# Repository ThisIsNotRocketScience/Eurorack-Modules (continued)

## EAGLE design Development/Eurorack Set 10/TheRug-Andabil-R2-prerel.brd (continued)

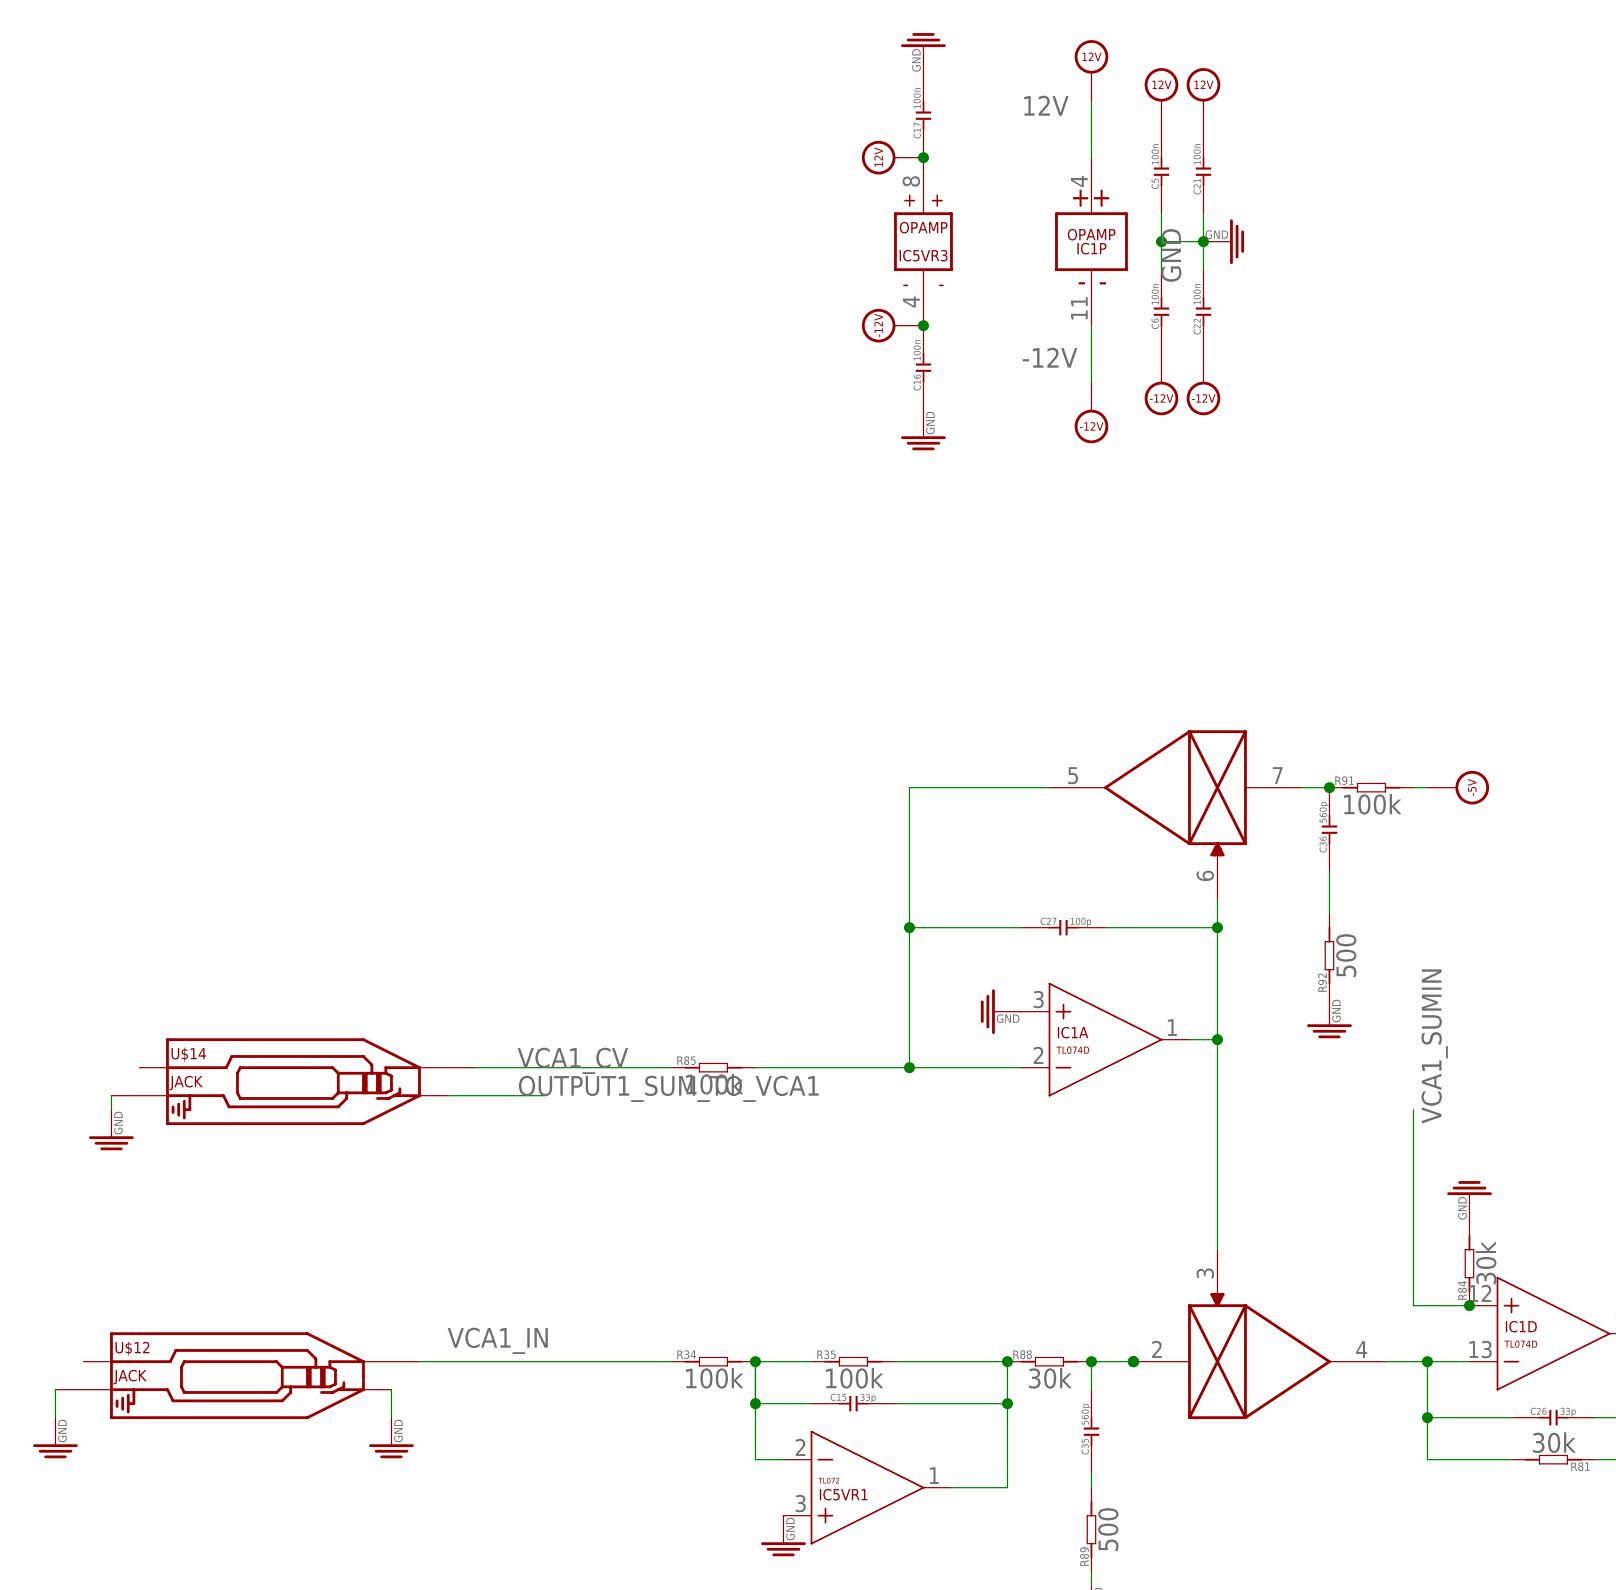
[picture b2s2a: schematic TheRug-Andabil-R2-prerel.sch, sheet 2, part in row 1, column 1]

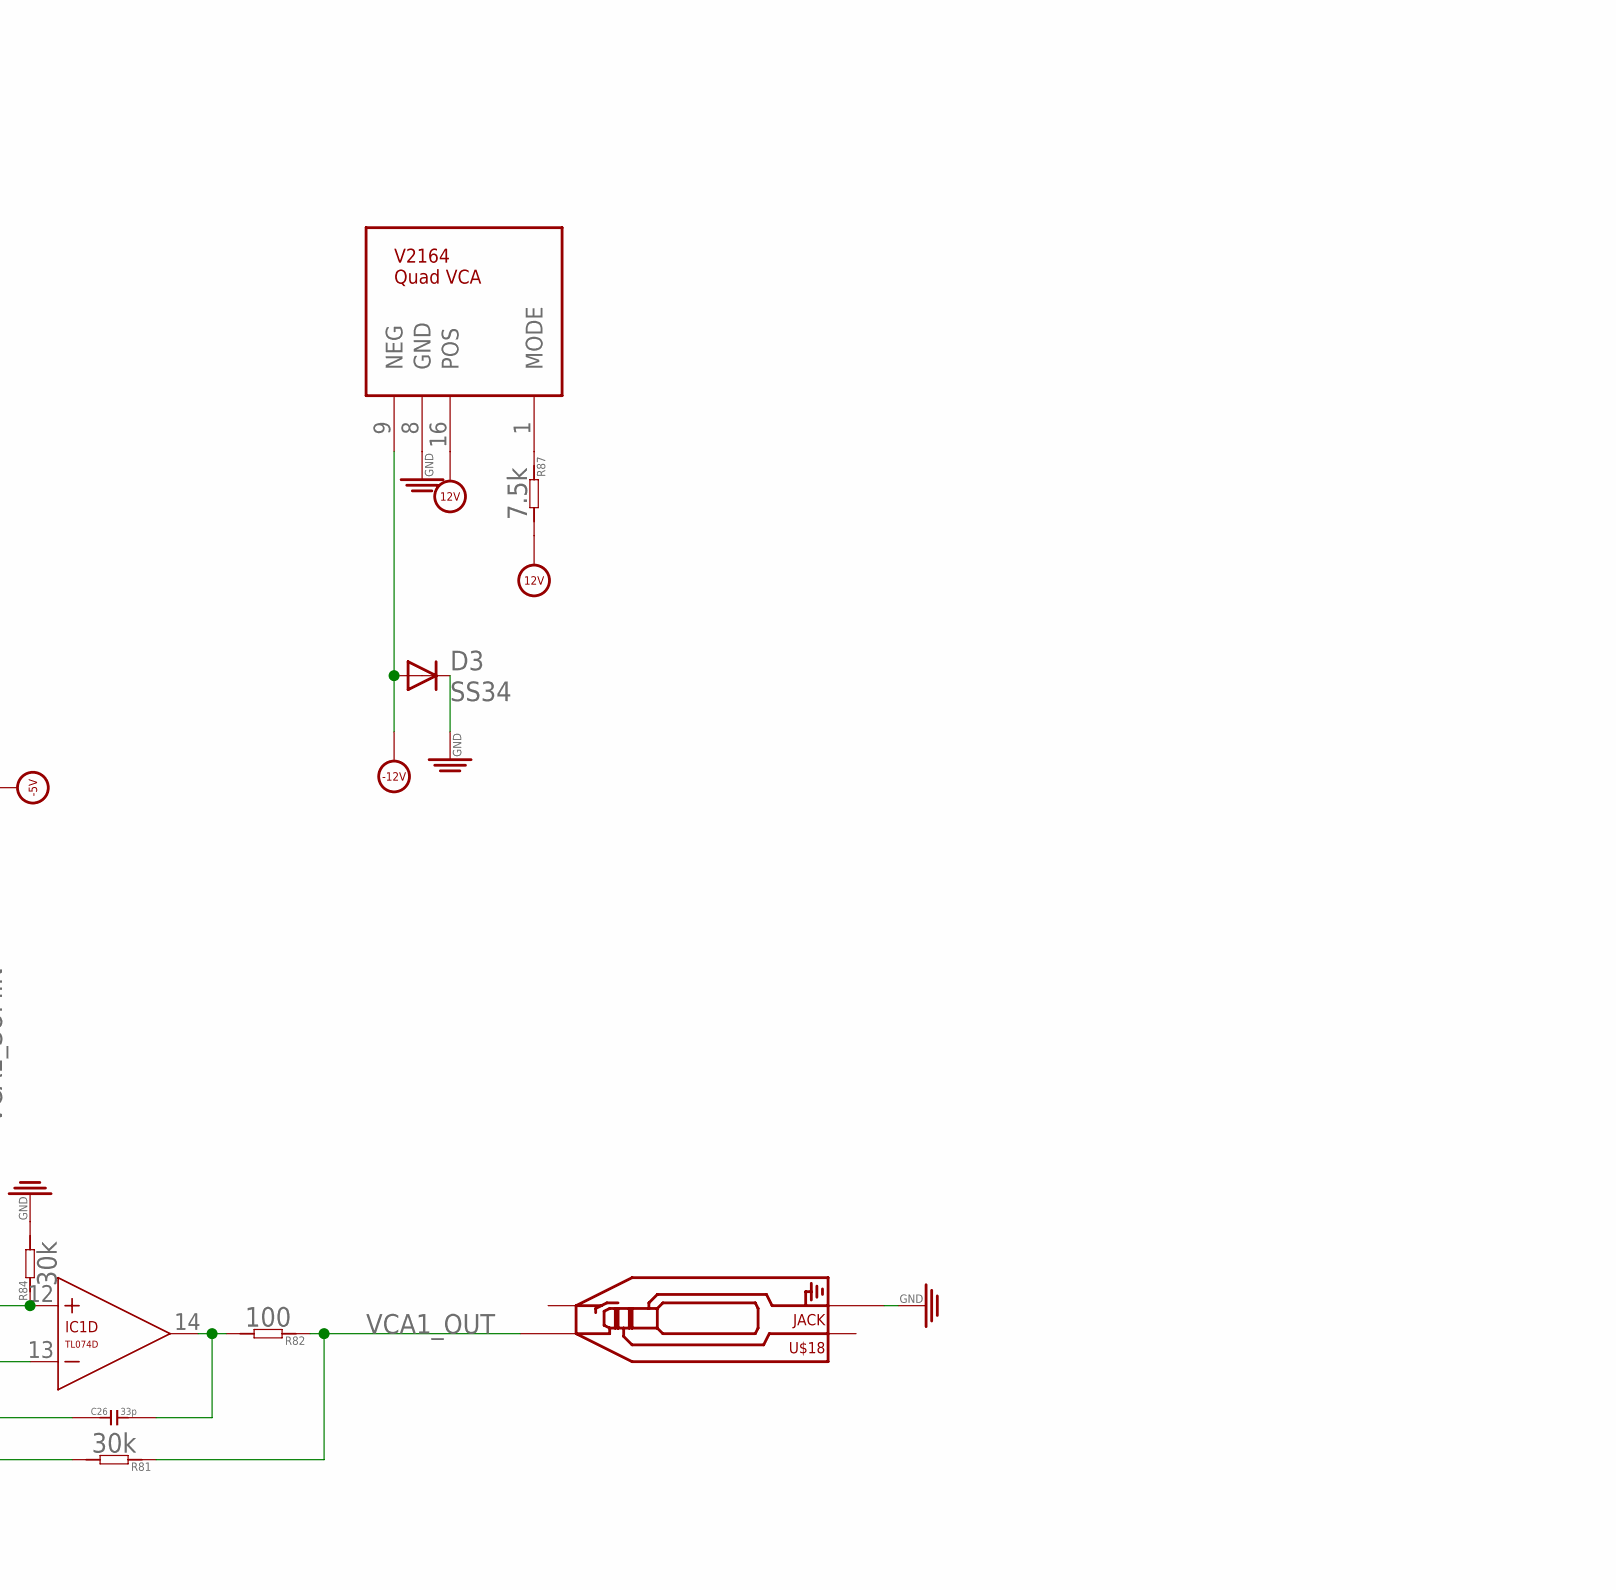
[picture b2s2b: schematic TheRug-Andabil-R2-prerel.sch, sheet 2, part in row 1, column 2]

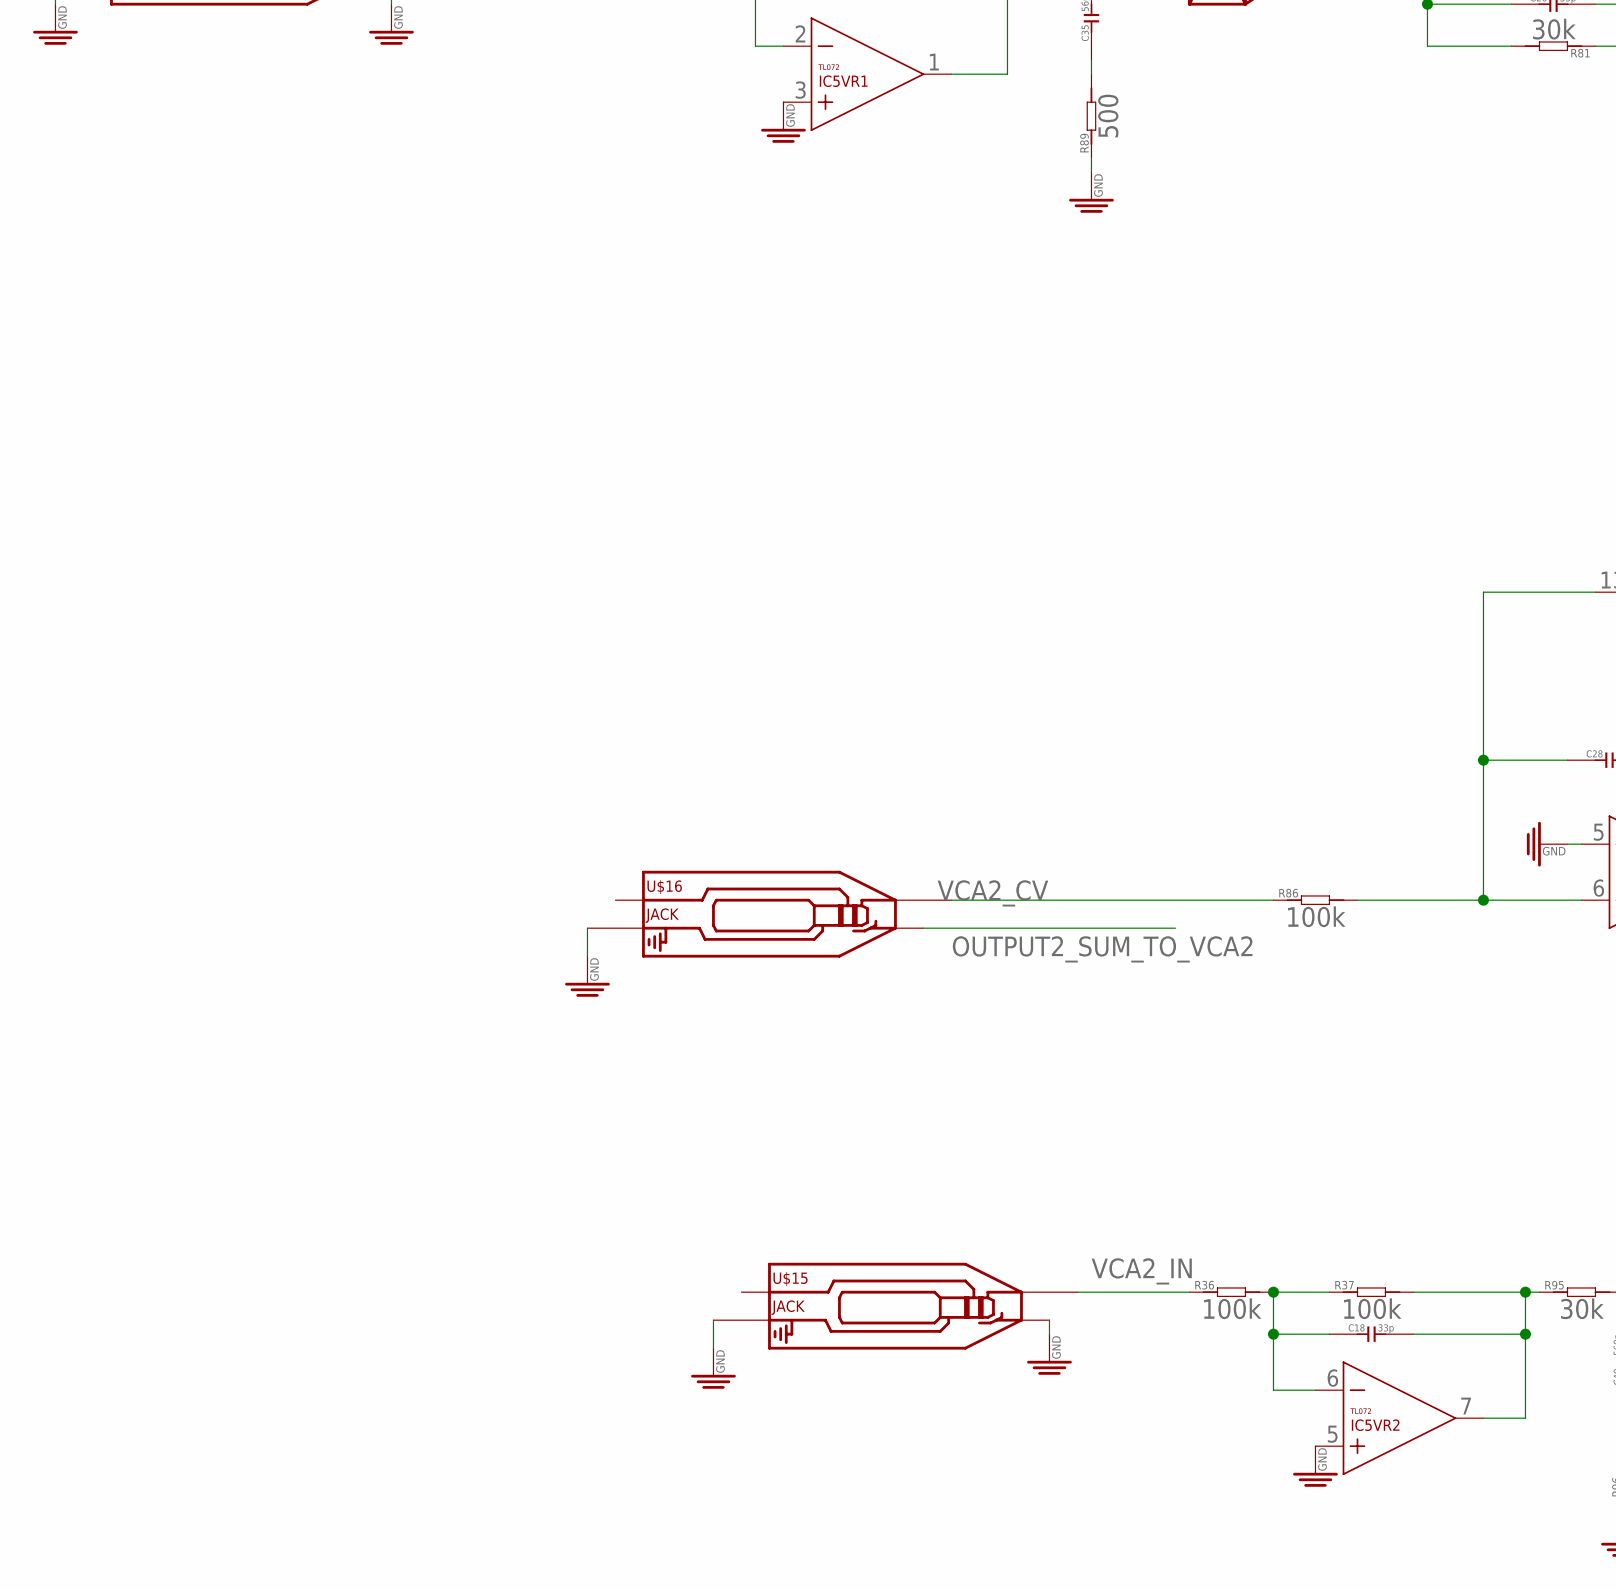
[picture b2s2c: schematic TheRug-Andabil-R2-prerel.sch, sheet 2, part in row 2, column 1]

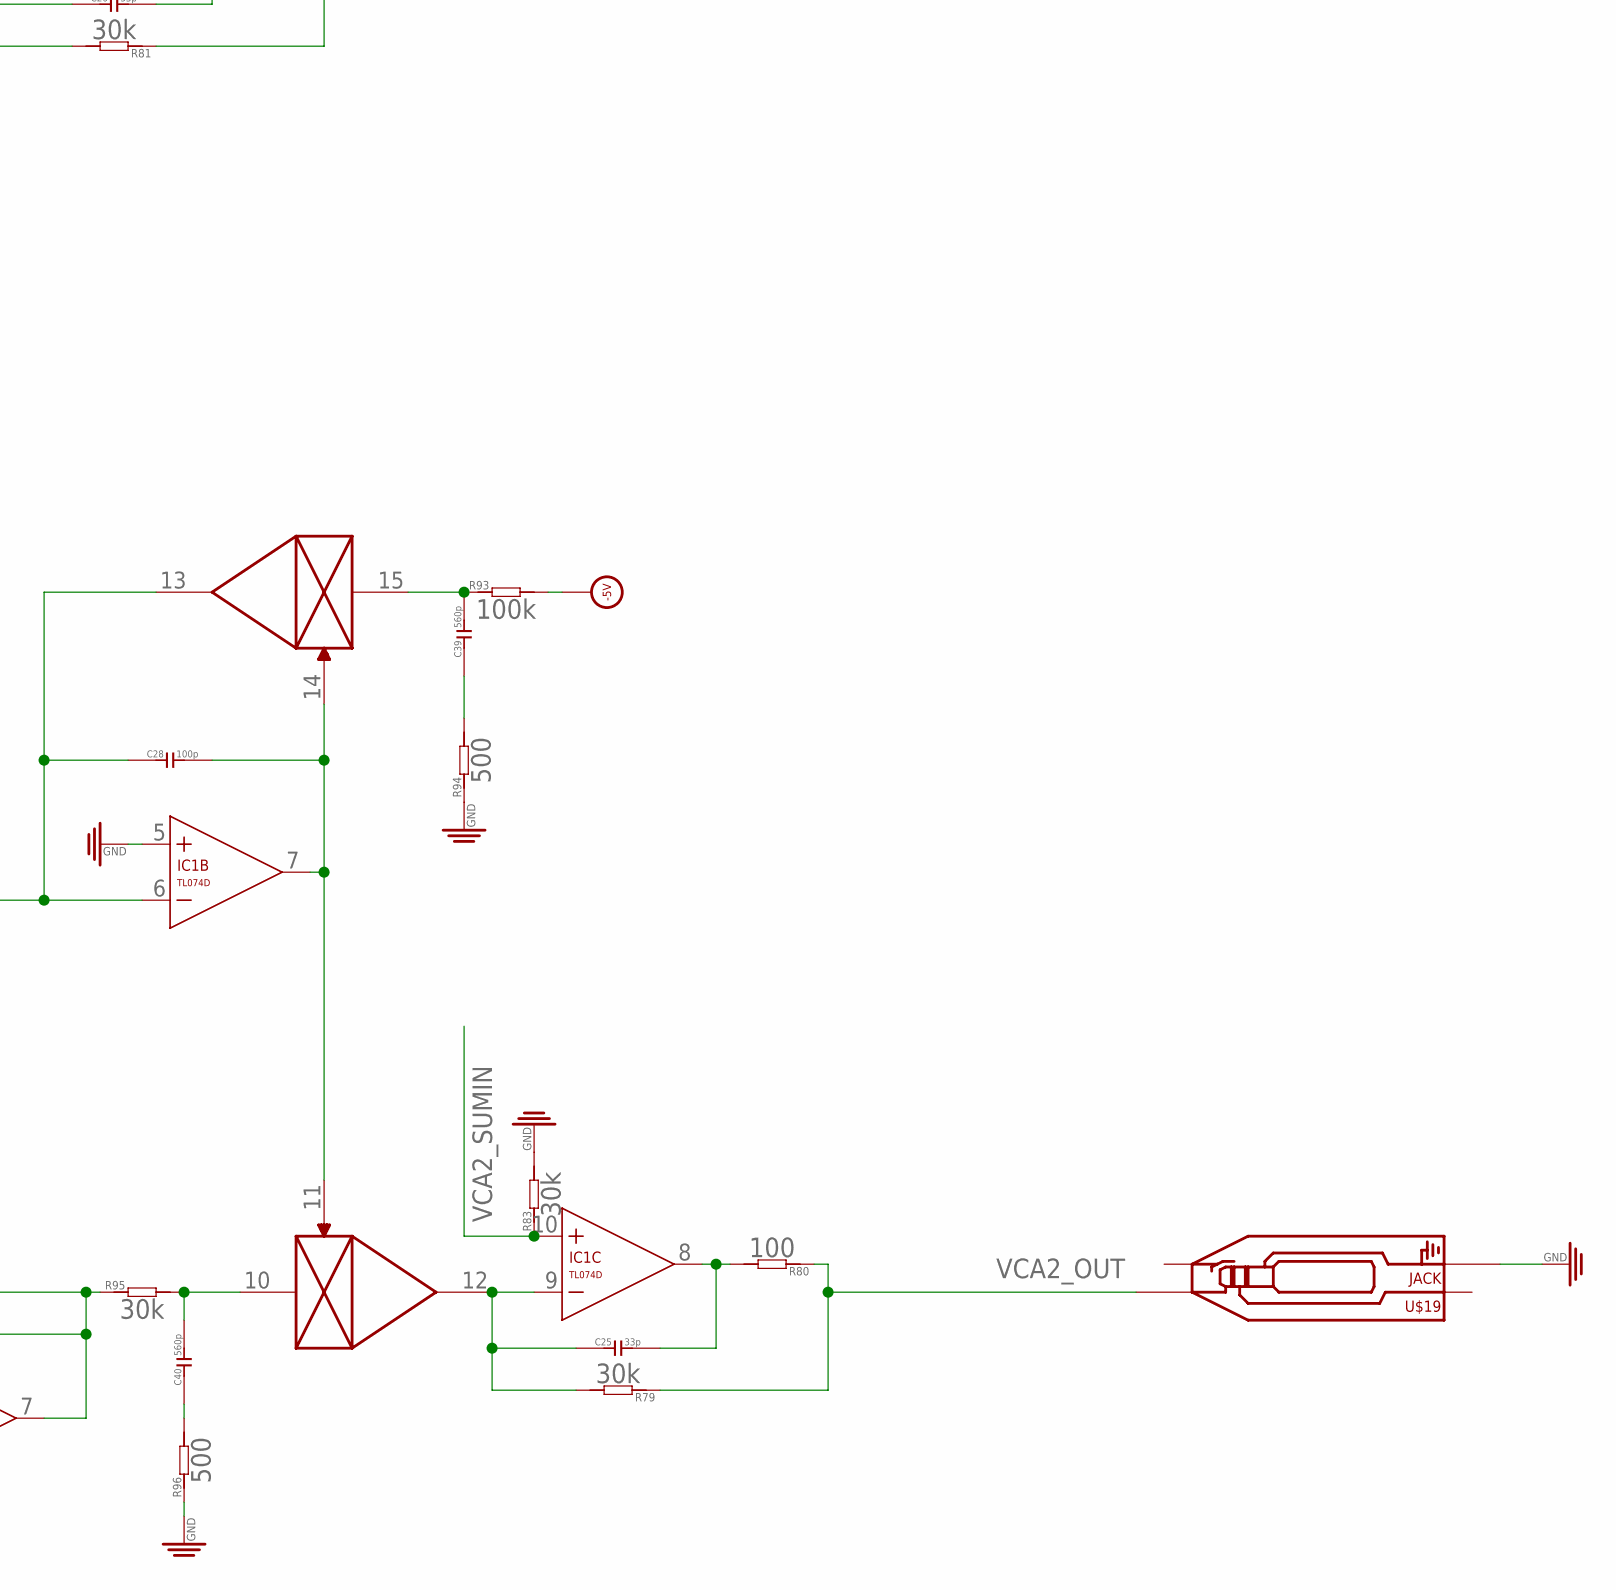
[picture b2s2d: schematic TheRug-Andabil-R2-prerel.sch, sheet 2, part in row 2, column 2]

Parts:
C5, C6, C16, C17, C21, C22: 100n; C0603
C15, C18, C25, C26: 33p; C0603
C27, C28: 100p; C0603
C35, C36, C39, C40: 560p; C0603
D3: SS34; DO-214AC
IC1: TL074D; SO14
IC5: TL072; SO08
R34, R35, R36, R37, R85, R86, R91, R93: 100k; R0603
R79, R81, R83, R84, R88, R95: 30k; R0603
R80, R82: 100; R0603
R87: 7.5k; R0603
R89, R92, R94, R96: 500; R0603
U$12, U$14, U$15, U$16, U$18, U$19: JACK; 3.5MM-JACK-SWITCH-13MM-NOHOLES
U$32: V2164; SO16

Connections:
12V: C5.2, C17.1, C21.2, IC1.4 (V+), IC5.8 (V+), R87.2, U$32.16 (POS); also elsewhere on the board
-5V: R91.2, R93.2; also elsewhere on the board
-12V: C6.1, C16.2, C22.1, D3.2 (A), IC1.11 (V-), IC5.4 (V-), U$32.9 (NEG); also elsewhere on the board
GND: C5.1, C6.2, C16.1, C17.2, C21.1, C22.2, D3.1 (C), IC1.3 (+IN), IC1.5 (+IN), IC5.3 (+IN), IC5.5 (+IN), R83.2, R84.2, R89.1, R92.1, R94.1, R96.1, U$12.RING_B@1 (RING), U$12.RING_T@3 (RING), U$12.SWITCH_B@1 (SWITCH), U$12.SWITCH_T@3 (SWITCH), U$14.RING_B@1 (RING), U$14.RING_T@3 (RING), U$15.RING_B@1 (RING), U$15.RING_T@3 (RING), U$15.SWITCH_B@1 (SWITCH), U$15.SWITCH_T@3 (SWITCH), U$16.RING_B@1 (RING), U$16.RING_T@3 (RING), U$18.RING_B@1 (RING), U$18.RING_T@3 (RING), U$19.RING_B@1 (RING), U$19.RING_T@3 (RING), U$32.8 (GND); also elsewhere on the board
unnamed: C15.1, IC5.2 (-IN), R34.2, R35.1
unnamed: C15.2, IC5.1 (OUT), R35.2, R88.1
unnamed: C18.1, IC5.6 (-IN), R36.2, R37.1
unnamed: C18.2, IC5.7 (OUT), R37.2, R95.1
unnamed: C25.2, IC1.8 (OUT), R80.2
unnamed: C25.1, IC1.9 (-IN), R79.2, U$32.12 (OUT)
unnamed: C26.2, IC1.14 (OUT), R82.2
unnamed: C26.1, IC1.13 (-IN), R81.2, U$32.4 (OUT)
unnamed: C27.2, IC1.1 (OUT), U$32.3 (CV), U$32.6 (CV)
unnamed: C28.1, IC1.6 (-IN), R86.2, U$32.13 (OUT)
unnamed: C28.2, IC1.7 (OUT), U$32.11 (CV), U$32.14 (CV)
unnamed: R87.1, U$32.1 (MODE)
unnamed: C35.1, R89.2
unnamed: C35.2, R88.2, U$32.2 (IN)
unnamed: C36.2, R91.1, U$32.7 (IN)
unnamed: C36.1, R92.2
unnamed: C39.2, R93.1, U$32.15 (IN)
unnamed: C39.1, R94.2
unnamed: C40.1, R96.2
unnamed: C40.2, R95.2, U$32.10 (IN)
OUTPUT1_SUM_TO_VCA1: U$14.SWITCH_B@1 (SWITCH), U$14.SWITCH_T@3 (SWITCH); also elsewhere on the board
OUTPUT2_SUM_TO_VCA2: U$16.SWITCH_B@1 (SWITCH), U$16.SWITCH_T@3 (SWITCH); also elsewhere on the board
VCA1_CV: R85.1, U$14.TIP_B@1 (TIP), U$14.TIP_T@3 (TIP)
VCA1_FB: C27.1, IC1.2 (-IN), R85.2, U$32.5 (OUT)
VCA1_IN: R34.1, U$12.TIP_B@1 (TIP), U$12.TIP_T@3 (TIP)
VCA1_OUT: R81.1, R82.1, U$18.TIP_B@1 (TIP), U$18.TIP_T@3 (TIP)
VCA1_SUMIN: IC1.12 (+IN), R84.1
VCA2_CV: R86.1, U$16.TIP_B@1 (TIP), U$16.TIP_T@3 (TIP)
VCA2_IN: R36.1, U$15.TIP_B@1 (TIP), U$15.TIP_T@3 (TIP)
VCA2_OUT: R79.1, R80.1, U$19.TIP_B@1 (TIP), U$19.TIP_T@3 (TIP)
VCA2_SUMIN: IC1.10 (+IN), R83.1

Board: 2 copper layers, 152 parts (1 on the bottom side), 94 nets, no tracks yet.

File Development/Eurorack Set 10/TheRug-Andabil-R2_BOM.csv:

Comment,Designator,Footprint,LCSC Part #
EURORACK_PCB12HP,"U$1",EURORACK12HPPCB,
MRA4004T3G,"D1, D2",DO-214AC,
10uF,"C11, C12",CASE-A_3216,
PJ-341,"U$2, U$4, U$13, U$3, U$5, U$6, U$17, U$12, U$14, U$15, U$16, U$18, U$19, U$9, U$20, U$25, U$26, U$27, U$28, U$30",3.5MM-JACK-SWITCH-13MM-NOHOLES,
100K 0.1%,"R1, R4, R5, R11, R12, R6, R7, R8, R9, R15, R16, R50, R52, R53, R55, R56, R58, R59, R60, R61, R64, R65",R0603,
100K,"R3, R22, R23, R51, R71, R72, R149, R147",R0603,
56,"R10, R13, R14, R17, R54, R62, R63, R66",R0603,
49.9K,"R2, R57",R0603,
1.2K,"R68, R40",R0603,
10k,"R148",R0603,
30k,"R79, R81, R83, R84, R88, R95",R0603,
100,"R80, R82",R0603,
100k,"R85, R86, R91, R93, R34, R35, R37, R36",R0603,
7.5k,"R87",R0603,
500,"R89, R92, R94, R96",R0603,
51k,"R24, R25, R26, R27, R28, R29, R30, R31, R32, R33",R0603,
10KB,"U$8, U$7, U$29, U$31",ALPS_POT_SQUAREHOLES,
3mm YELLOW,"D_1NEG, D_1POS, D_2NEG, D_2POS",3MMLED,
22pf,"C7, C8, C9, C10, C13, C29, C30, C31, C32, C33",C0603,
100nF,"C49, C23, C24, C37, C38, C1, C2, C3, C4",C0603,
100n,"C5, C6, C21, C22, C16, C17",C0603,
33p,"C25, C26, C15, C18",C0603,
100p,"C27, C28",C0603,
560p,"C35, C36, C39, C40",C0603,
POWERSHROUDED,"J1",POWER_16_SHROUDED,
LM4040DIM3-5.0,"U2",SOT95P237X112-3N,
TL074TSSOP14,"IC4, IC11, IC2, IC3, IC1",TSSOP14,
V2164,"U$32",SO16,
TL072TSSOP8,"IC5",TSSOP8,

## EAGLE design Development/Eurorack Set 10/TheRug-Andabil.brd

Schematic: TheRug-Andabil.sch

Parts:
C1, C2, C3, C4, C5, C6, C15, C16, C17, C18, C19, C20, C21, C22, C25, C26, C27, C28, C35, C36, C42, C50: 100nF; C0603
C7, C8, C9, C10, C13, C14, C29, C30, C31, C32, C33, C34: 22pf; C0603
C11, C12: 10uF; CASE-A_3216
C49: 100nF; C0603; MPN 06035C104KAT2A
D1, D2: MRA4004T3G; DO-214AC; MPN US1G-E3/5AT
D7, D8: MRA4004T3G; SOD123; MPN US1G-E3/5AT
D_1NEG, D_1POS, D_2NEG, D_2POS: 3mm YELLOW; 3MMLED
IC1, IC2, IC3, IC7, IC8, IC9, IC10, IC12: TL072; SO08
IC5, IC6: TL074D; SO14
J1: POWERSHROUDED; POWER_16_SHROUDED
Q1, Q2: MMBT3906LT1SMD; SOT23-BEC
R1, R4, R5, R6, R7, R8, R9, R11, R12, R15, R16, R50, R52, R53, R55, R56, R58, R59, R60, R61, R64, R65: 100K 0.1%; R0603
R2, R24, R26, R57: 49.9K; R0603
R3, R19, R20, R22, R23, R27, R28, R42, R49, R51, R68, R69, R71, R72, R73, R74, R147, R149: 100K; R0603
R10, R13, R14, R17, R54, R62, R63, R66: 56; R0603
R18, R21, R67, R70: 1k; R0603
R25, R39, R40, R41: 499; R0603
R29, R30, R32, R33: 220K; R0603
R31, R38: 249K; R0603
R34, R36: 30.1K; R0603
R35, R37: 100; R0603
R43, R44, R46, R48: 2K; R0603
R45, R47: 200; R0603
R75, R76, R77, R78: 100k; TRIMPOT
R148: 10k; R0603
U1: LM13700M; SOIC127P620X175-16N
U2: LM4040DIM3-5.0; SOT95P237X112-3N
U$1: EURORACK_PCB12HP; EURORACK12HPPCB
U$2, U$6, U$9, U$12, U$13, U$14, U$15, U$16, U$25, U$28: PJ-341; 3.5MM-JACK-SWITCH-13MM-INPUT
U$3, U$4, U$5, U$17, U$18, U$19, U$20, U$26, U$27, U$30: PJ-341; 3.5MM-JACK-SWITCH-13MM-OUTPUT
U$7, U$8, U$29, U$31: 10KB; ALPS_POT_SQUAREHOLES

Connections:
5V: IC12.7 (OUT), R75.P$3, R76.P$3, R77.P$3, R78.P$3, R149.2, U$8.P$3 (A), U$29.P$3 (A)
12V: C1.2, C3.2, C5.2, C11.+ (1), C15.2, C17.2, C19.1, C21.2, C25.2, C27.2, C35.2, C50.2, D1.2 (-), IC1.8 (V+), IC2.8 (V+), IC3.8 (V+), IC5.4 (V+), IC6.4 (V+), IC7.8 (V+), IC8.8 (V+), IC9.8 (V+), IC10.8 (V+), IC12.8 (V+), R31.1, R38.1, U1.11 (V+)
-5V: IC12.1 (OUT), IC12.2 (-IN), R75.P$1, R76.P$1, R77.P$1, R78.P$1, R147.1, U$8.P$1 (E), U$29.P$1 (E)
-5VIN: C49.2, IC12.3 (+IN), R148.2, U2.2 (ANODE)
-5V_TO_5V: IC12.6 (-IN), R147.2, R149.1
-12V: C2.1, C4.1, C6.1, C12.- (2), C16.1, C18.1, C20.2, C22.1, C26.1, C28.1, C36.1, C42.1, D2.1 (+), IC1.4 (V-), IC2.4 (V-), IC3.4 (V-), IC5.11 (V-), IC6.11 (V-), IC7.4 (V-), IC8.4 (V-), IC9.4 (V-), IC10.4 (V-), IC12.4 (V-), R148.1, U1.6 (V-)
CV_IN_A: Q1.C, U1.16 (AMP_BIAS_IN)
CV_IN_B: Q2.C, U1.1 (AMP_BIAS_IN_2)
GND: C1.1, C2.2, C3.1, C4.2, C5.1, C6.2, C11.- (2), C12.+ (1), C15.1, C16.2, C17.1, C18.2, C19.2, C20.1, C21.1, C22.2, C25.1, C26.2, C27.1, C28.2, C35.1, C36.2, C42.2, C49.1, C50.1, D_1NEG.+, D_1POS.-, D_2NEG.+, D_2POS.-, IC1.3 (+IN), IC1.5 (+IN), IC2.3 (+IN), IC2.5 (+IN), IC3.3 (+IN), IC3.5 (+IN), IC5.3 (+IN), IC5.10 (+IN), IC5.12 (+IN), IC6.3 (+IN), IC6.10 (+IN), IC6.12 (+IN), IC7.3 (+IN), IC7.5 (+IN), IC8.3 (+IN), IC8.5 (+IN), IC9.3 (+IN), IC9.5 (+IN), IC12.5 (+IN), J1.3 (GND), J1.4 (GND), J1.5 (GND), J1.6 (GND), J1.7 (GND), J1.8 (GND), R25.1, R39.1, R40.1, R41.1, R45.2, R47.2, U2.1 (CATHODE), U$2.RING@3 (RING), U$2.SWITCH@3 (SWITCH), U$3.RING@3 (RING), U$4.RING@3 (RING), U$5.RING@3 (RING), U$6.RING@3 (RING), U$6.SWITCH@3 (SWITCH), U$7.P$3 (A), U$9.RING@3 (RING), U$9.SWITCH@3 (SWITCH), U$12.RING@3 (RING), U$12.SWITCH@3 (SWITCH), U$13.RING@3 (RING), U$13.SWITCH@3 (SWITCH), U$14.RING@3 (RING), U$15.RING@3 (RING), U$15.SWITCH@3 (SWITCH), U$16.RING@3 (RING), U$17.RING@3 (RING), U$18.RING@3 (RING), U$19.RING@3 (RING), U$20.RING@3 (RING), U$25.RING@3 (RING), U$25.SWITCH@3 (SWITCH), U$26.RING@3 (RING), U$27.RING@3 (RING), U$28.RING@3 (RING), U$28.SWITCH@3 (SWITCH), U$30.RING@3 (RING), U$31.P$3 (A)
unnamed: IC10.5 (+IN), U$7.P$2 (S)
unnamed: C8.2, IC3.1 (OUT), R10.1, R12.2
unnamed: IC10.7 (OUT), R2.1, R22.2
unnamed: R23.1, U$6.TIP@3 (TIP), U$7.P$1 (E)
unnamed: C9.1, IC2.2 (-IN), R6.2, R8.1
unnamed: R3.1, U$8.P$2 (S)
unnamed: C7.2, IC1.1 (OUT), R1.2, R6.1, R7.1, R11.1, R20.1
unnamed: C8.1, IC3.2 (-IN), R11.2, R12.1
unnamed: C10.1, IC2.6 (-IN), R7.2, R9.1
unnamed: IC10.6 (-IN), R22.1, R23.2
unnamed: C9.2, IC2.1 (OUT), R8.2, R13.1
unnamed: R4.1, U$13.TIP@3 (TIP)
unnamed: IC6.1 (OUT), R24.1, R73.1
unnamed: C7.1, IC1.2 (-IN), R1.1, R2.2, R3.2, R4.2, R5.2
unnamed: R13.2, U$3.TIP@3 (TIP)
unnamed: R14.2, U$5.TIP@3 (TIP)
unnamed: C13.1, IC3.6 (-IN), R15.1, R16.2
unnamed: C13.2, IC3.7 (OUT), R16.1, R17.1
unnamed: R17.2, U$17.TIP@3 (TIP)
unnamed: R5.1, U$2.TIP@3 (TIP)
unnamed: D_1POS.+, R21.1
unnamed: R10.2, U$4.TIP@3 (TIP)
unnamed: D_1NEG.-, R18.1
unnamed: C14.2, IC1.7 (OUT), R18.2, R19.1, R21.2
unnamed: C14.1, IC1.6 (-IN), R19.2, R20.2
unnamed: R37.2, U$18.TIP@3 (TIP)
unnamed: IC5.14 (OUT), R36.2, R37.1
unnamed: D1.1 (+), J1.9 (+12V), J1.10 (+12V)
unnamed: R31.2, U1.2 (DIODE_BIAS_2)
unnamed: R38.2, U1.15 (DIODE_BIAS)
unnamed: R35.2, U$19.TIP@3 (TIP)
unnamed: IC6.14 (OUT), R34.2, R35.1
unnamed: R33.1, R75.P$2
unnamed: R32.1, R77.P$2
unnamed: R30.1, R76.P$2
unnamed: R29.1, R78.P$2
unnamed: R27.2, U$12.TIP@3 (TIP)
unnamed: R74.2, U$15.TIP@3 (TIP)
unnamed: IC5.2 (-IN), R27.1, R28.2
unnamed: IC5.1 (OUT), R26.1, R28.1
unnamed: R25.2, R26.2, U1.13 (-IN)
unnamed: R24.2, R39.2, U1.4 (-IN_2)
unnamed: R33.2, R40.2, U1.14 (+IN)
unnamed: R30.2, R41.2, U1.3 (+IN_2)
unnamed: R49.1, U$16.TIP@3 (TIP)
unnamed: R42.1, U$14.TIP@3 (TIP)
unnamed: IC6.2 (-IN), R73.2, R74.1
unnamed: IC5.9 (-IN), R42.2, R43.1
unnamed: IC5.5 (+IN), IC5.8 (OUT), R43.2
unnamed: D7.-, IC5.6 (-IN), R32.2, R44.1
unnamed: C30.2, IC9.1 (OUT), R54.1, R56.2
unnamed: R51.1, U$29.P$2 (S)
unnamed: D7.+, IC5.7 (OUT), Q1.B
unnamed: Q1.E, R44.2, R45.1
unnamed: D8.-, IC6.6 (-IN), R29.2, R46.1
unnamed: D8.+, IC6.7 (OUT), Q2.B
unnamed: Q2.E, R46.2, R47.1
unnamed: IC6.5 (+IN), IC6.8 (OUT), R48.2
unnamed: IC6.9 (-IN), R48.1, R49.2
unnamed: R52.1, U$25.TIP@3 (TIP)
unnamed: D2.2 (-), J1.1 (-12V), J1.2 (-12V)
unnamed: C29.1, IC7.2 (-IN), R50.1, R51.2, R52.2, R53.2, R57.2
unnamed: R54.2, U$20.TIP@3 (TIP)
unnamed: C29.2, IC7.1 (OUT), R50.2, R55.1, R58.1, R59.1, R69.1
unnamed: C30.1, IC9.2 (-IN), R55.2, R56.1
unnamed: R53.1, U$9.TIP@3 (TIP)
unnamed: R72.1, U$28.TIP@3 (TIP), U$31.P$1 (E)
unnamed: C31.1, IC8.2 (-IN), R58.2, R60.1
unnamed: C32.1, IC8.6 (-IN), R59.2, R61.1
unnamed: C31.2, IC8.1 (OUT), R60.2, R62.1
unnamed: R62.2, U$26.TIP@3 (TIP)
unnamed: R63.2, U$27.TIP@3 (TIP)
unnamed: C33.1, IC9.6 (-IN), R64.1, R65.2
unnamed: C33.2, IC9.7 (OUT), R65.1, R66.1
unnamed: R66.2, U$30.TIP@3 (TIP)
unnamed: D_2NEG.-, R67.1
unnamed: C34.2, IC7.7 (OUT), R67.2, R68.1, R70.2
unnamed: C34.1, IC7.6 (-IN), R68.2, R69.2
unnamed: D_2POS.+, R70.1
unnamed: IC10.3 (+IN), U$31.P$2 (S)
unnamed: IC10.1 (OUT), R57.1, R71.2
unnamed: IC10.2 (-IN), R71.1, R72.2
OUTPUT1_SUM_TO_VCA1: C10.2, IC2.7 (OUT), R9.2, R14.1, R15.2, U$14.SWITCH@3 (SWITCH)
OUTPUT2_SUM_TO_VCA2: C32.2, IC8.7 (OUT), R61.2, R63.1, R64.2, U$16.SWITCH@3 (SWITCH)
TRANS_OUT_A: IC5.13 (-IN), R36.1, U1.5 (OUT)
TRANS_OUT_B: IC6.13 (-IN), R34.1, U1.12 (OUT_2)

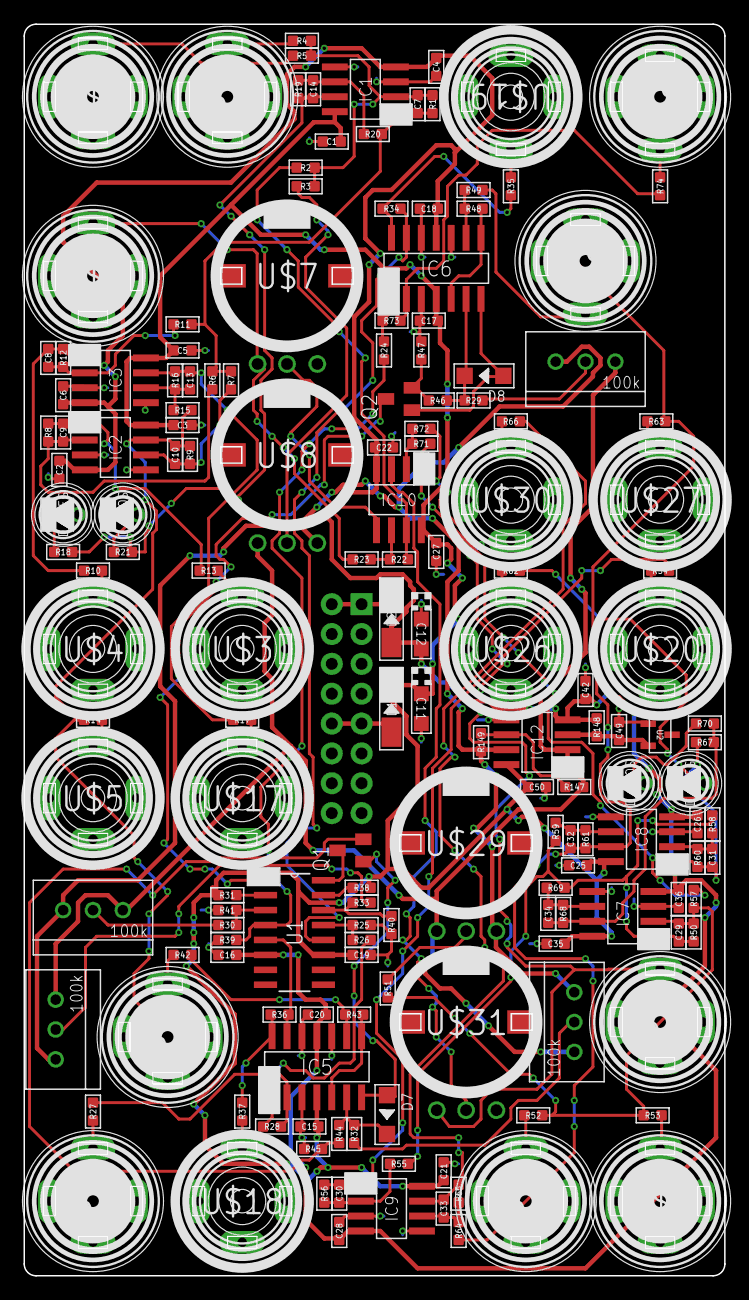
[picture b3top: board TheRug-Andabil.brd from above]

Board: 2 copper layers, 59.6 x 106.5 mm, 166 parts (1 on the bottom side), 95 nets.
